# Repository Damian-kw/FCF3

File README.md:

# FCF3
Flight controler for qudrocopter based on STM32F3 mcu (IN PROGRESS)
1.Controller architecture

2. PCB

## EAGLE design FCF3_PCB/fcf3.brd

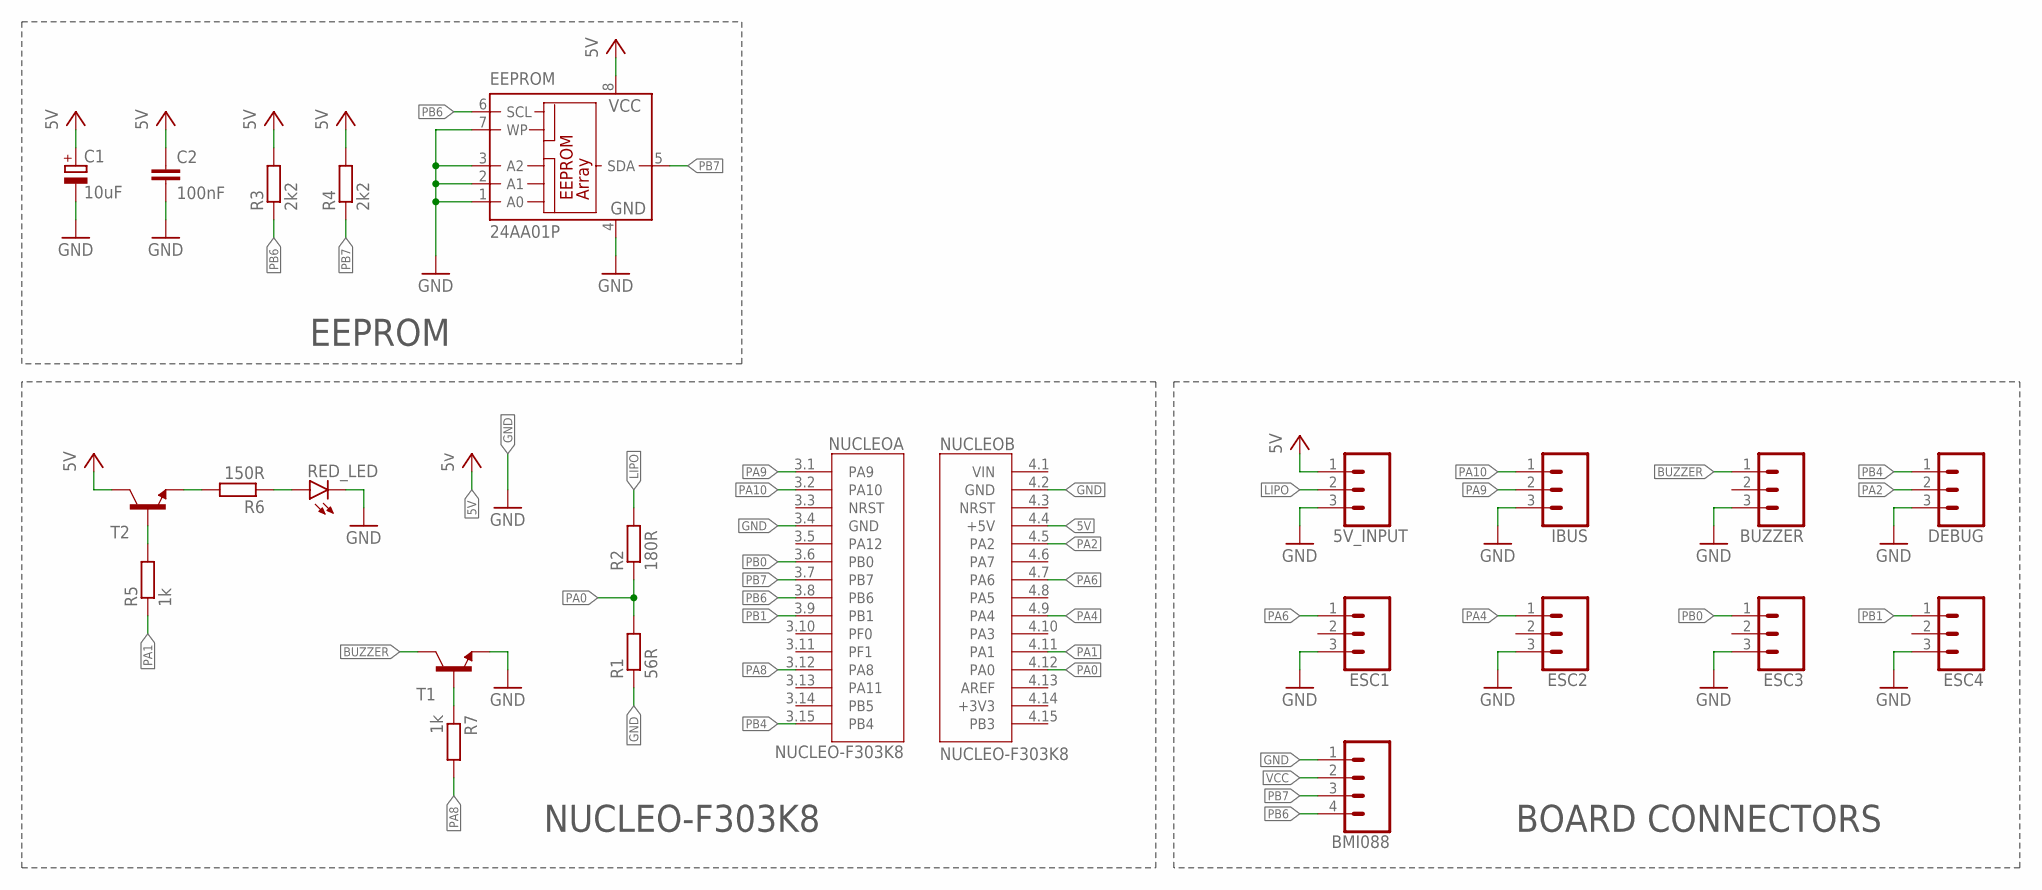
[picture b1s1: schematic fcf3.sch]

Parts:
5V_INPUT: CONN_03; 1X03
BMI088: CONN_04; 1X04
BUZZER: CONN_03; 1X03
C1: 10uF; E2-5
C2: 100nF; C025-024X044
DEBUG: CONN_03; 1X03
EEPROM: 24AA01P; DIL8
ESC1, ESC2, ESC3, ESC4: CONN_03; 1X03
IBUS: CONN_03; 1X03
NUCLEO: NUCLEO-F303K8; MODULE_NUCLEO-F303K8
R1: 56R; 0207/10
R2: 180R; 0207/10
R3, R4: 2k2; 0207/10
R5, R7: 1k; 0207/10
R6: 150R; 0207/10
RED_LED: LED3MM
T1, T2: -NPN-TO92; TO92

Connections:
5V: NUCLEO.4.4 (+5V)
BUZZER: BUZZER.1, T1.3 (C)
GND: 5V_INPUT.3, BMI088.1, BUZZER.3, C1.-, C2.2, DEBUG.3, EEPROM.1 (A0), EEPROM.2 (A1), EEPROM.3 (A2), EEPROM.4 (GND), EEPROM.7 (WP), ESC1.3, ESC2.3, ESC3.3, ESC4.3, IBUS.3, NUCLEO.3.4 (GND), NUCLEO.4.2 (GND), R1.1, RED_LED.K (C), T1.1 (E)
LIPO: 5V_INPUT.2, R2.2
unnamed: R5.2, T2.2 (B)
unnamed: R6.2, T2.1 (E)
unnamed: R6.1, RED_LED.A
unnamed: R7.1, T1.2 (B)
PA0: NUCLEO.4.12 (PA0), R1.2, R2.1
PA1: NUCLEO.4.11 (PA1), R5.1
PA2: DEBUG.2, NUCLEO.4.5 (PA2)
PA4: ESC2.1, NUCLEO.4.9 (PA4)
PA6: ESC1.1, NUCLEO.4.7 (PA6)
PA8: NUCLEO.3.12 (PA8), R7.2
PA9: IBUS.2, NUCLEO.3.1 (PA9)
PA10: IBUS.1, NUCLEO.3.2 (PA10)
PB0: ESC3.1, NUCLEO.3.6 (PB0)
PB1: ESC4.1, NUCLEO.3.9 (PB1)
PB4: DEBUG.1, NUCLEO.3.15 (PB4)
PB6: BMI088.4, EEPROM.6 (SCL), NUCLEO.3.8 (PB6), R3.1
PB7: BMI088.3, EEPROM.5 (SDA), NUCLEO.3.7 (PB7), R4.1
VCC: 5V_INPUT.1, BMI088.2, C1.+, C2.1, EEPROM.8 (VCC), R3.2, R4.2, T2.3 (C)

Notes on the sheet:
NUCLEO-F303K8
EEPROM
BOARD CONNECTORS

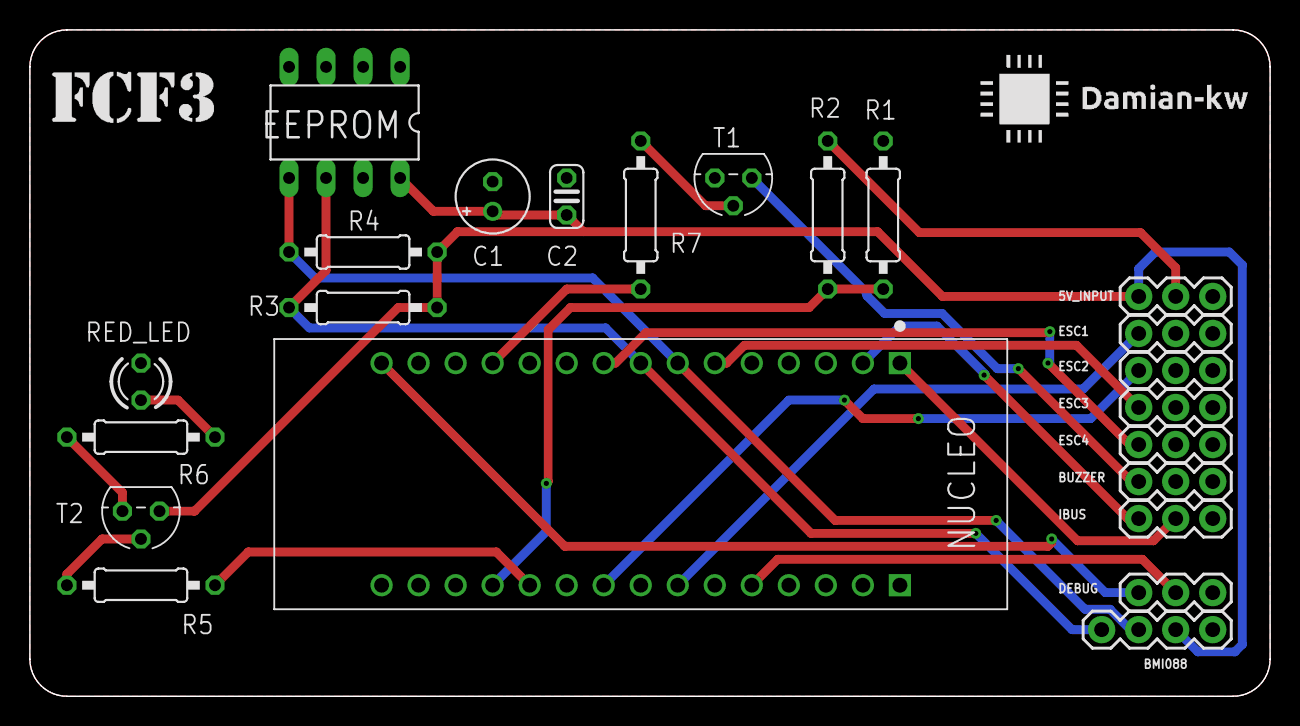
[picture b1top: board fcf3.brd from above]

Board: 2 copper layers, 85.1 x 45.7 mm, 23 parts (0 on the bottom side), 21 nets.

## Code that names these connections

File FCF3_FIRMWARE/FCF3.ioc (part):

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Mcu.Name=STM32F303K(6-8)Tx
Mcu.Package=LQFP32
Mcu.UserName=STM32F303K8Tx
PA0.GPIOParameters=GPIO_Label
PA0.GPIO_Label=lipo
PA0.Mode=IN1-Single-Ended
PA0.Signal=ADC1_IN1
PA1.GPIOParameters=GPIO_Speed,GPIO_Label
PA1.GPIO_Label=error_led
PA1.GPIO_Speed=GPIO_SPEED_FREQ_MEDIUM
PA1.Signal=GPIO_Output
PA10.Mode=Asynchronous
PA10.Signal=USART1_RX
PA13.GPIOParameters=GPIO_Label
PA13.GPIO_Label=SWDIO
PA13.Mode=Serial_Wire
PA13.Signal=SYS_JTMS-SWDIO
PA14.GPIOParameters=GPIO_Label
PA14.GPIO_Label=SWCLK
PA14.Mode=Serial_Wire
PA14.Signal=SYS_JTCK-SWCLK
PA2.GPIOParameters=GPIO_Label
PA2.GPIO_Label=VCP_TX
PA2.Mode=Asynchronous
PA2.Signal=USART2_TX
PA4.Signal=S_TIM3_CH2
PA6.Signal=S_TIM3_CH1
PA8.GPIOParameters=PinState,GPIO_Label
PA8.GPIO_Label=buzzer
PA8.PinState=GPIO_PIN_SET
PA8.Signal=GPIO_Output
PA9.Mode=Asynchronous
PA9.Signal=USART1_TX
PB0.Signal=S_TIM3_CH3
PB1.Signal=S_TIM3_CH4
PB4.GPIOParameters=GPIO_Label
PB4.GPIO_Label=VCP_RX
PB4.Mode=Asynchronous
PB4.Signal=USART2_RX
PB6.Mode=I2C
PB6.Signal=I2C1_SCL
PB7.Mode=I2C
PB7.Signal=I2C1_SDA
PF0\ /\ OSC_IN.GPIOParameters=GPIO_Label
PF0\ /\ OSC_IN.GPIO_Label=MCO
PF0\ /\ OSC_IN.Mode=HSE-External-Clock-Source
PF0\ /\ OSC_IN.Signal=RCC_OSC_IN
RCC.HSEPLLFreq_Value=8000000
RCC.HSE_VALUE=8000000
RCC.SYSCLKFreq_VALUE=64000000
RCC.SYSCLKSourceVirtual=RCC_SYSCLKSOURCE_PLLCLK
board=NUCLEO-F303K8
boardIOC=true

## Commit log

2019-12-28 adding files
2019-12-28 adding images
2019-12-28 fixing small bugs
2020-01-22 adding unit tests
2020-01-22 writing unit tests for salloc module
2020-01-22 writing unit tests for salloc
2020-01-30 small changes

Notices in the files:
parts and their libraries:
SparkFun-Connectors: Licensing: Creative Commons ShareAlike 4.0 International - https://creativecommons.org/licenses/by-sa/4.0
